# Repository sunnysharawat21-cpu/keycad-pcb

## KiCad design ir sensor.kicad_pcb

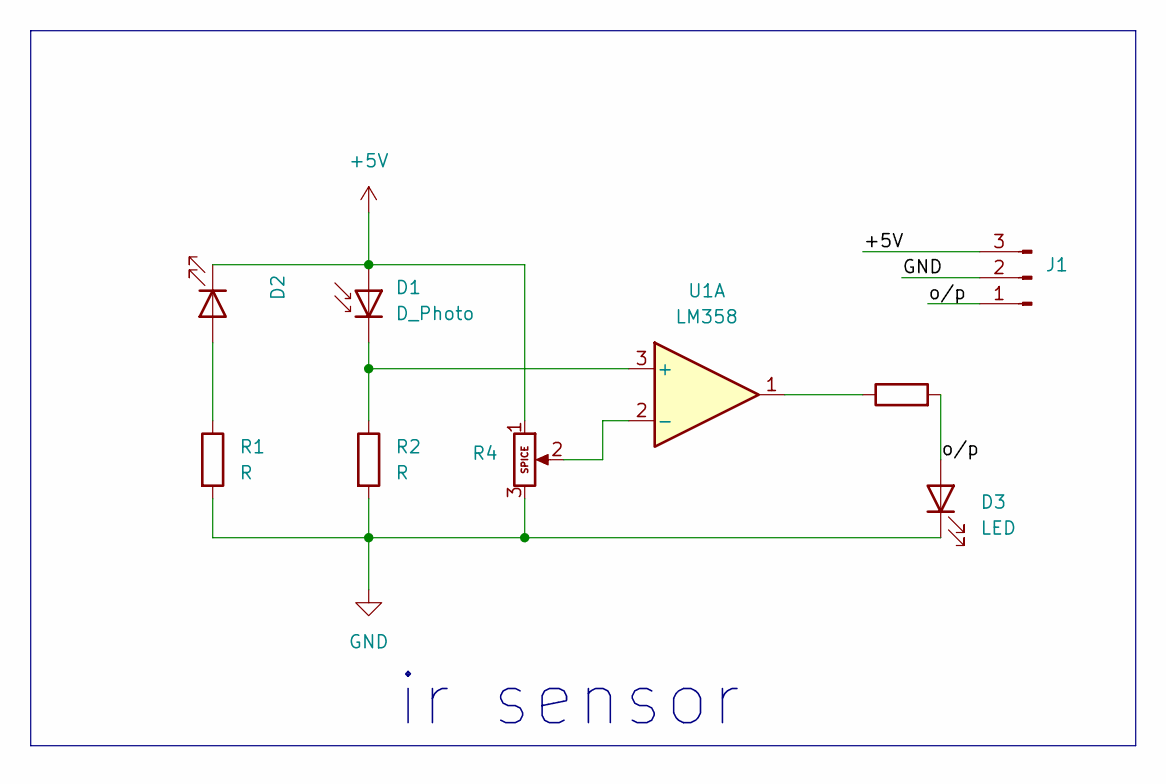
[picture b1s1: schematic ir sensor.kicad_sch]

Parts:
D1: D_Photo; LED_1W_3W_R8
D2: IR26-21C_L110_TR8; LED_1206_3216Metric
D3: LED; LED_1W_3W_R8
J1: Conn_01x03_Pin; PinHeader_1x03_P2.54mm_Vertical
R1, R2, R3: R; R_0805_2012Metric
R4: Potentiometer; Potentiometer_ACP_CA9-VSMD_Vertical
U1: LM358; SOIC-8-1EP_3.9x4.9mm_P1.27mm_EP2.514x3.2mm

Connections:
+5V: D1.2 (A), D2.1 (K), J1.3, R4.1
/o/p: D3.2 (A), J1.1, R3.2
GND: D3.1 (K), J1.2, R1.2, R2.2, R4.3
unnamed: D1.1 (K), R2.1, U1.3 (+)
unnamed: D2.2 (A), R1.1
unnamed: R3.1, U1.1
unnamed: R4.2, U1.2 (-)

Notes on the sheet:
ir sensor

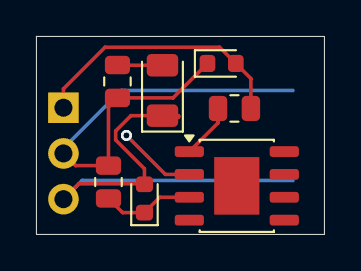
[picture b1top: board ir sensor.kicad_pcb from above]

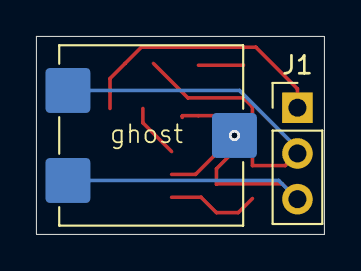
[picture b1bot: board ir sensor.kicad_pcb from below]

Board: 2 copper layers, 16.0 x 11.0 mm, 9 parts (2 on the bottom side), 7 nets.
